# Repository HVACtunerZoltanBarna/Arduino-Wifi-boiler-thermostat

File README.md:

# Arduino-Wifi-boiler-thermostat
Tested, Super stable Arduino thermostat board, with Wifi board.
I wanted to build something like an industrilal system with arduinos. 
This project has to boards. One is R3 UNO, other is R4 UNO WIFI.
The R3 controls the boiler relay, and checks flow/ return/ room temperatures. 
Watchdog running on the R3 so if the code is frozen, then it restartes itself.
R4 wifi runs heartbeat signal. If R4 is frozen then R3 restarts it.
R4 also emits "CloudOK" signal. (for example cloud is unreachable, or wifi is off, or just R4 is dropped off from Wifi). If this signal is false for certain time, then R3 restarts it.
The setpoint is arrives from the Cloud, and uploads to the R3. If nothing arrives then R3 runs from the latest setpoint. If no wifi and the power just came back, the default settemp is 14°C.
If R3 founds error  (for example bad sensor, or no heating) if forwards the error towards the R4 which uploads it to the cloud.

You can download the code and the circuit diagram too.
The circuit diagram contains a tested blackout circuit too. (if the VIN voltage is too low then it pulls down the Reset pin of the R3).
PLS  give me some feedback see how it works in the huge world. :)
Sincerely: Zoltán.

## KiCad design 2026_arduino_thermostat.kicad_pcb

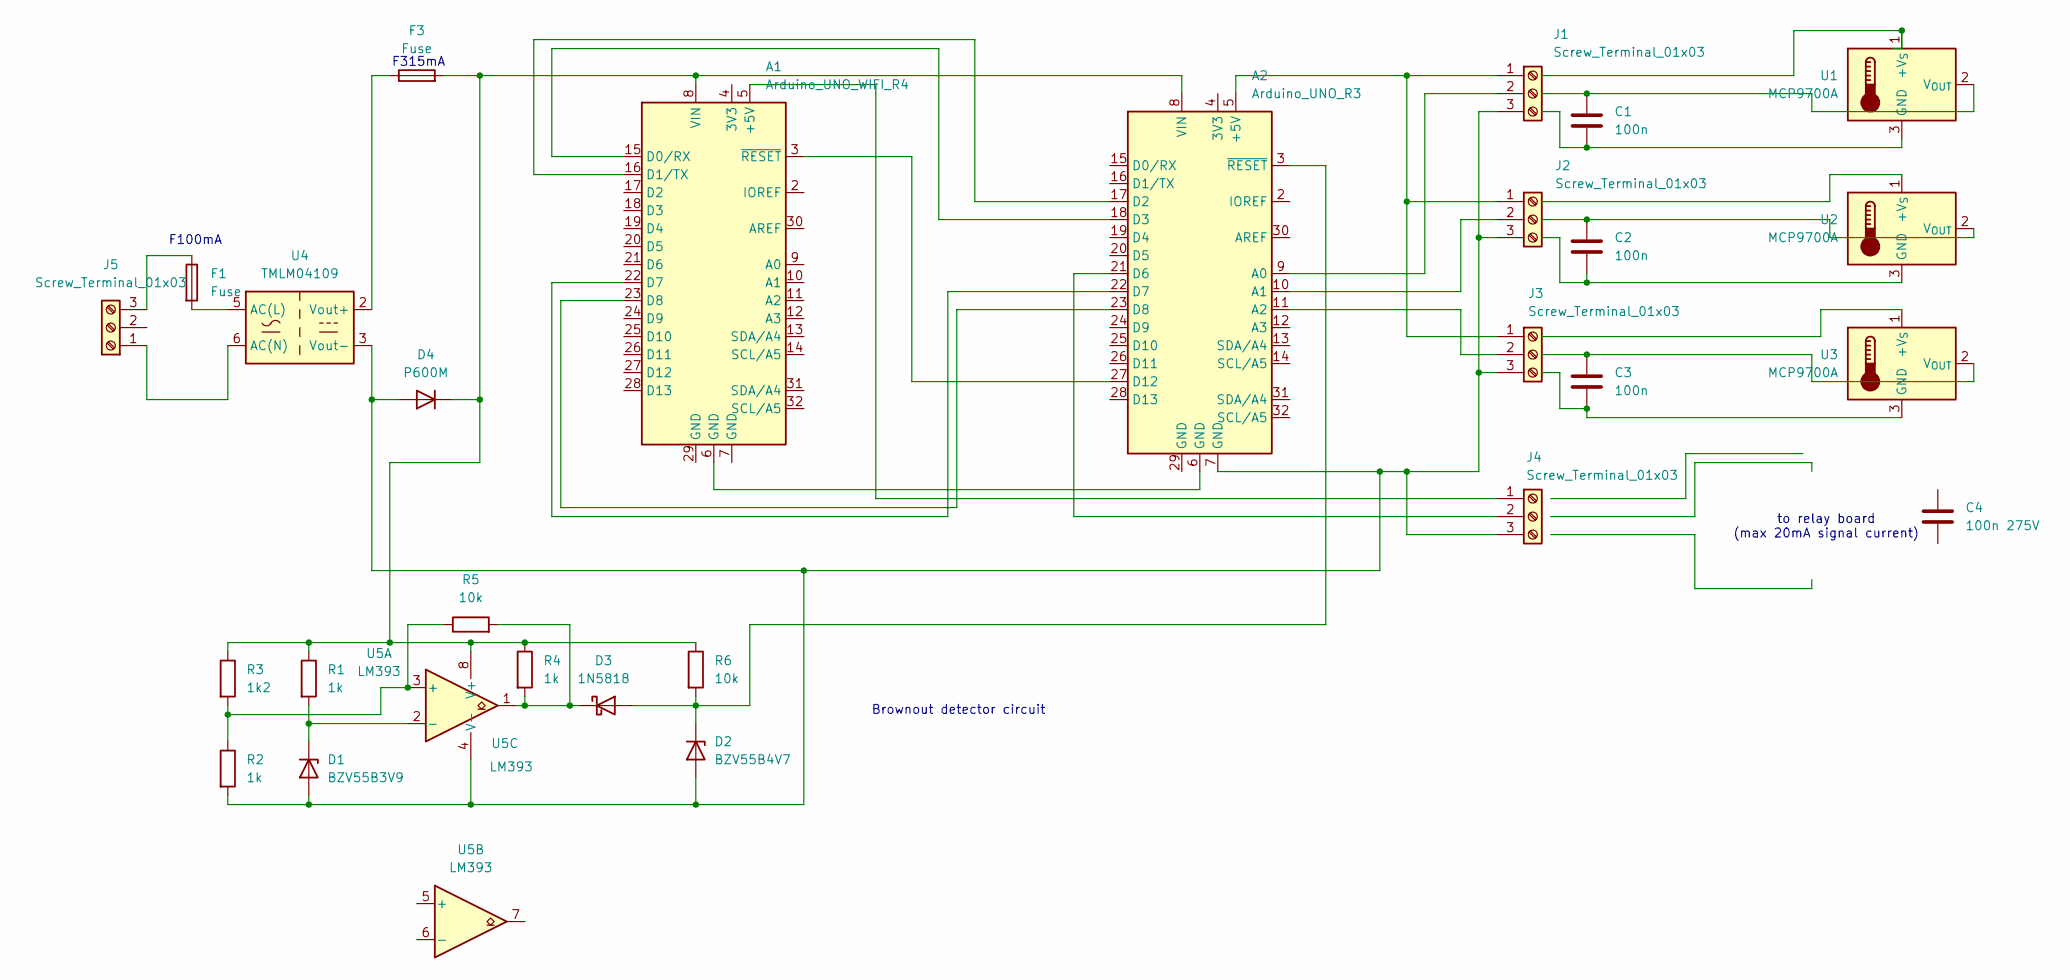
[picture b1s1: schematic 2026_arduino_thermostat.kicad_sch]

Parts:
A1: Arduino_UNO_WIFI_R4; Arduino_UNO_R3
A2: Arduino_UNO_R3
C1, C2, C3: 100n; C_Disc_D7.5mm_W4.4mm_P5.00mm
C4: 100n 275V
D1: BZV55B3V9; D_A-405_P7.62mm_Horizontal
D2: BZV55B4V7; D_A-405_P7.62mm_Horizontal
D3: 1N5818; D_DO-35_SOD27_P7.62mm_Horizontal
D4: P600M; D_5W_P12.70mm_Horizontal
F1: Fuse; Littelfuse_Package_H_XBN2MM
F3: Fuse; Fuseholder_Littelfuse_445_030_series_5x25mm
J1, J2, J3, J4, J5: Screw_Terminal_01x03; Tag-Connect_TC2030-IDC-FP_2x03_P1.27mm_Vertical
R1, R2, R4: 1k; R_Axial_DIN0204_L3.6mm_D1.6mm_P7.62mm_Horizontal
R3: 1k2; R_Axial_DIN0204_L3.6mm_D1.6mm_P7.62mm_Horizontal
R5, R6: 10k; R_Axial_DIN0204_L3.6mm_D1.6mm_P7.62mm_Horizontal
U1, U2, U3: MCP9700A; TO-92_Inline
U4: TMLM04109; Converter_ACDC_TRACO_TMLM-04_THT
U5: LM393; DIP-8_W7.62mm

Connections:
unnamed: A1.5 (+5V), J4.1
unnamed: A1.15 (D0/RX), A2.18 (D3)
unnamed: A1.16 (D1/TX), A2.17 (D2)
unnamed: A1.22 (D7), A2.22 (D7)
unnamed: A1.23 (D8), A2.23 (D8)
unnamed: A1.6 (GND), A2.6 (GND)
unnamed: A1.8 (VIN), A2.8 (VIN), D4.1 (K), F3.2, R1.1, R3.1, R4.1, R6.1, U5.8 (V+)
unnamed: A1.3 (~RESET), A2.27 (D12)
unnamed: A2.5 (+5V), J1.1, J2.1, J3.1
unnamed: A2.9 (A0), J1.2
unnamed: A2.10 (A1), J2.2
unnamed: A2.11 (A2), J3.2
unnamed: A2.21 (D6), J4.2
unnamed: A2.3 (~RESET), D2.1 (K), D3.2 (A), R6.2
unnamed: A2.7 (GND), D1.2 (A), D2.2 (A), D4.2 (A), J1.3, J2.3, J3.3, J4.3, R2.2, U4.3 (Vout-), U5.4 (V-)
unnamed: D1.1 (K), R1.2, U5.2 (-)
unnamed: D3.1 (K), R4.2, R5.2, U5.1
unnamed: J5.1, U4.6 (AC(N))
unnamed: F1.1, J5.3
unnamed: C1.2, U1.3 (GND)
unnamed: C1.1, U1.2 (V_{OUT})
unnamed: C2.2, U2.3 (GND)
unnamed: C2.1, U2.2 (V_{OUT})
unnamed: C3.2, U3.3 (GND)
unnamed: C3.1, U3.2 (V_{OUT})
unnamed: F1.2, U4.5 (AC(L))
unnamed: F3.1, U4.2 (Vout+)
unnamed: R2.1, R3.2, R5.1, U5.3 (+)

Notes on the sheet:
F315mA
to relay board (max 20mA signal current)
F100mA
Brownout detector circuit

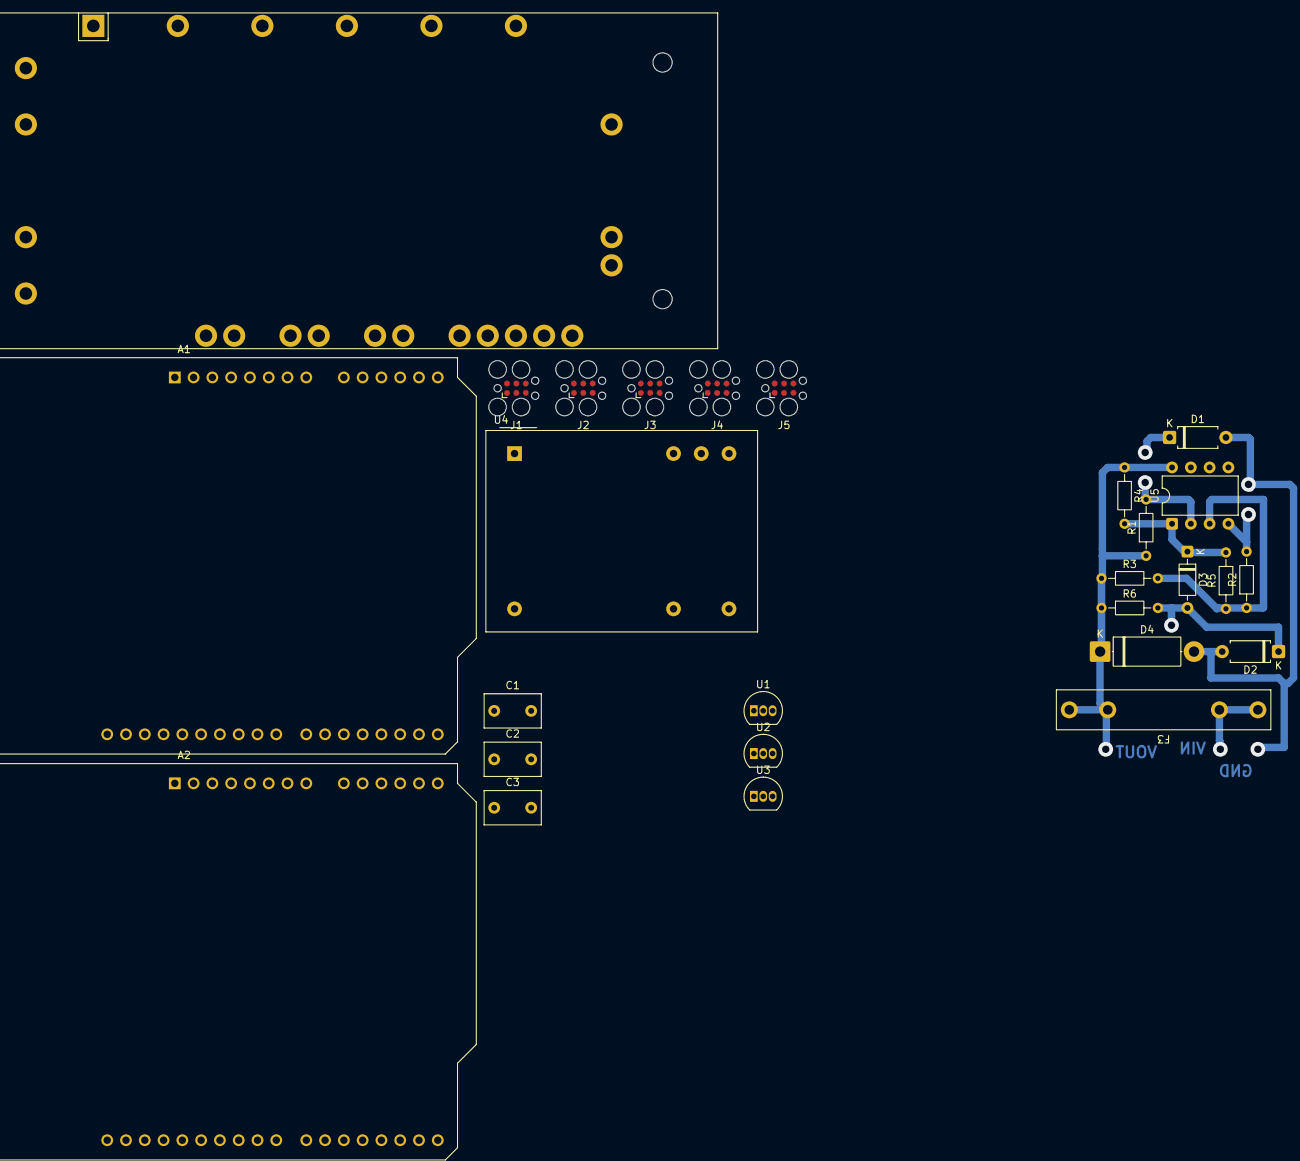
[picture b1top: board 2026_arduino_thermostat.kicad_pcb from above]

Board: 2 copper layers, 27 parts (0 on the bottom side), 28 nets.
